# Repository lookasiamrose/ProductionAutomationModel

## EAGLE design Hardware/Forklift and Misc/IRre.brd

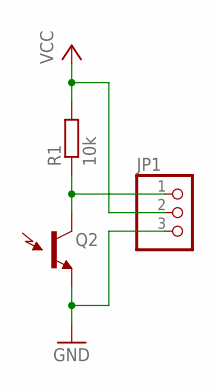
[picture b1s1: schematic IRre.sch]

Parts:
JP1: PINHD-1X3; 1X03
Q2: LTR-301
R1: 10k; R0805

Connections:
GND: JP1.3, Q2.E (E1)
unnamed: JP1.1, Q2.C (C1), R1.1
VCC: JP1.2, R1.2

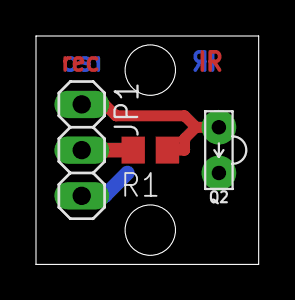
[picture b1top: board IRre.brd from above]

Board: 2 copper layers, 12.4 x 12.7 mm, 3 parts (0 on the bottom side), 3 nets.

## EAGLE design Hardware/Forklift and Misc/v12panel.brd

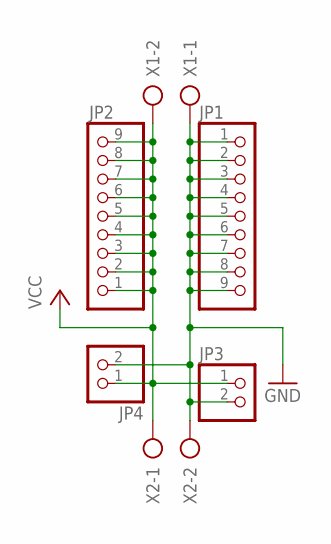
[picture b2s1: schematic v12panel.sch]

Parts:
JP1, JP2: PINHD-1X9; 1X09
JP3, JP4: PINHD-1X2; 1X02
X1, X2: AK500/2

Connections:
GND: JP1.1, JP1.2, JP1.3, JP1.4, JP1.5, JP1.6, JP1.7, JP1.8, JP1.9, JP3.2, JP4.2, X1.1, X2.2
VCC: JP2.1, JP2.2, JP2.3, JP2.4, JP2.5, JP2.6, JP2.7, JP2.8, JP2.9, JP3.1, JP4.1, X1.2, X2.1

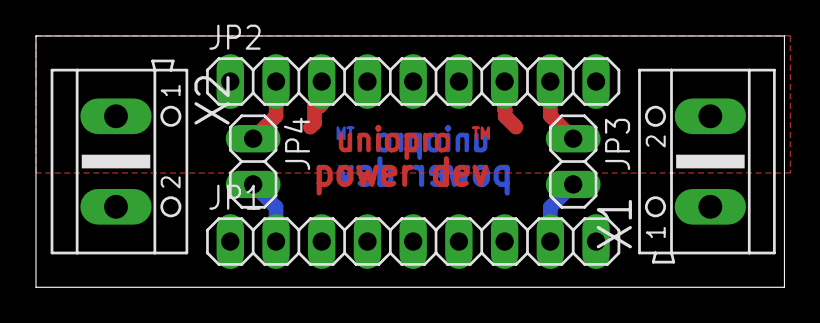
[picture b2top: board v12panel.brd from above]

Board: 2 copper layers, 41.6 x 14.0 mm, 6 parts (0 on the bottom side), 2 nets.

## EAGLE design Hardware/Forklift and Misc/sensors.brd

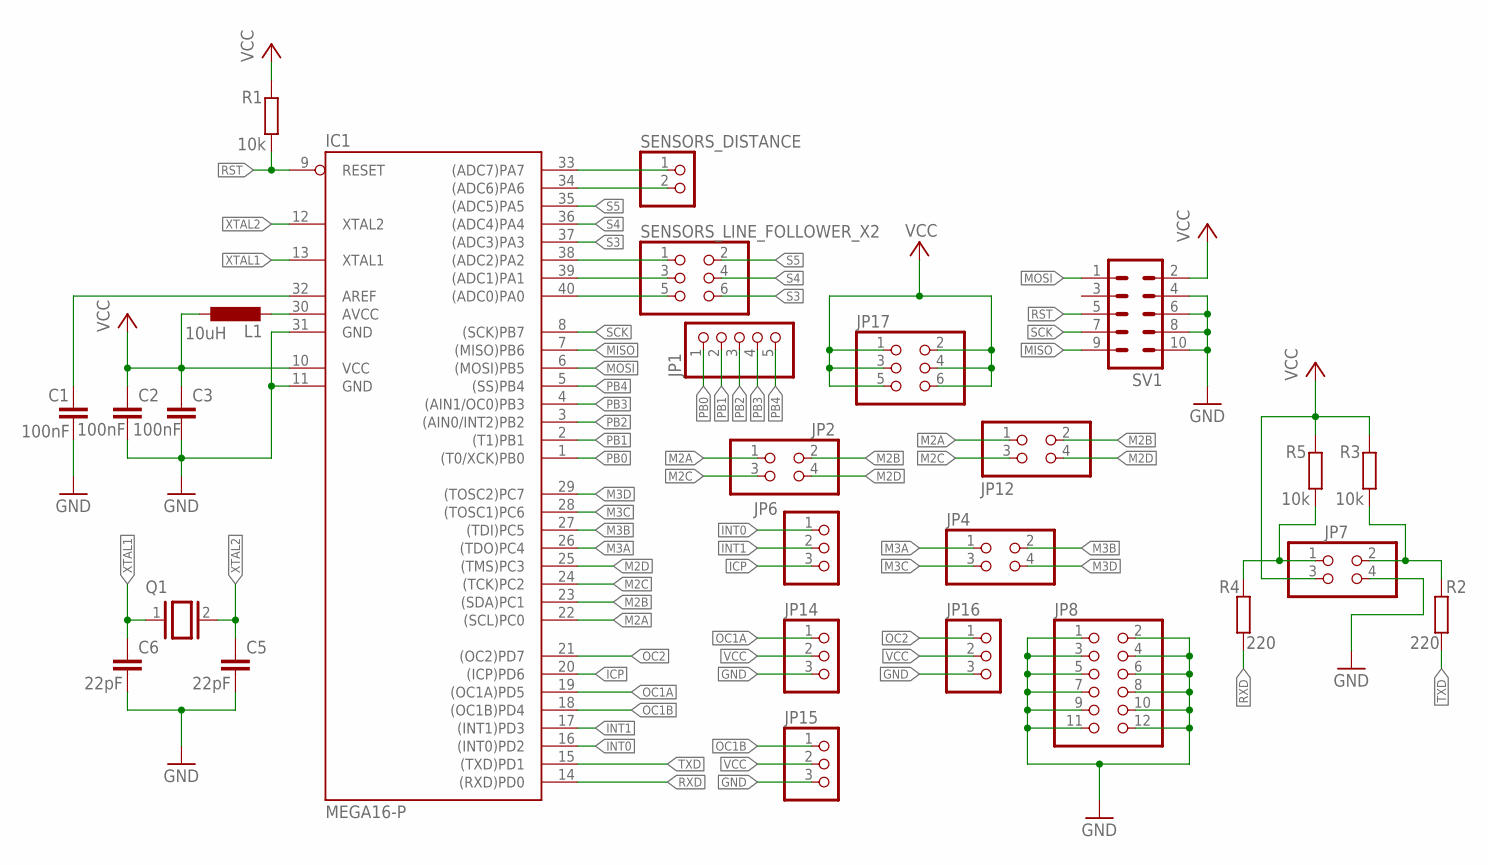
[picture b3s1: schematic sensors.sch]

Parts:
C1, C2, C3: 100nF; C0805
C5, C6: 22pF; C0805
IC1: MEGA16-P; DIL40
JP1: PINHD-1X5; 1X05
JP2, JP4, JP7, JP12: PINHD-2X2; 2X02
JP6, JP14, JP15, JP16: PINHD-1X3; 1X03
JP8: PINHD-2X6; 2X06
JP17: PINHD-2X3; 2X03
L1: 10uH; 0207/7
Q1: XTAL/S; QS
R1, R3, R5: 10k; R0805
R2, R4: 220; R0805
SENSORS_DISTANCE: PINHD-1X2; 1X02
SENSORS_LINE_FOLLOWER_X2: PINHD-2X3; 2X03
SV1: ML10

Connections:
ADC6: IC1.34 ((ADC6)PA6), SENSORS_DISTANCE.2
GND: C1.2, C2.2, C3.2, C5.2, C6.2, IC1.11 (GND), IC1.31 (GND), JP7.4, JP8.1, JP8.2, JP8.3, JP8.4, JP8.5, JP8.6, JP8.7, JP8.8, JP8.9, JP8.10, JP8.11, JP8.12, JP14.3, JP15.3, JP16.3, SV1.4, SV1.6, SV1.8, SV1.10
ICP: IC1.20 ((ICP)PD6), JP6.3
INT0: IC1.16 ((INT0)PD2), JP6.1
INT1: IC1.17 ((INT1)PD3), JP6.2
M2A: IC1.22 ((SCL)PC0), JP2.1, JP12.1
M2B: IC1.23 ((SDA)PC1), JP2.2, JP12.2
M2C: IC1.24 ((TCK)PC2), JP2.3, JP12.3
M2D: IC1.25 ((TMS)PC3), JP2.4, JP12.4
M3A: IC1.26 ((TDO)PC4), JP4.1
M3B: IC1.27 ((TDI)PC5), JP4.2
M3C: IC1.28 ((TOSC1)PC6), JP4.3
M3D: IC1.29 ((TOSC2)PC7), JP4.4
MISO: IC1.7 ((MISO)PB6), SV1.9
MOSI: IC1.6 ((MOSI)PB5), SV1.1
unnamed: JP7.1, R4.2, R5.1
unnamed: JP7.2, R2.2, R3.1
unnamed: C1.1, IC1.32 (AREF)
unnamed: IC1.30 (AVCC), L1.2
unnamed: IC1.33 ((ADC7)PA7), SENSORS_DISTANCE.1
OC1A: IC1.19 ((OC1A)PD5), JP14.1
OC1B: IC1.18 ((OC1B)PD4), JP15.1
OC2: IC1.21 ((OC2)PD7), JP16.1
PB0: IC1.1 ((T0/XCK)PB0), JP1.1
PB1: IC1.2 ((T1)PB1), JP1.2
PB2: IC1.3 ((AIN0/INT2)PB2), JP1.3
PB3: IC1.4 ((AIN1/OC0)PB3), JP1.4
PB4: IC1.5 ((SS)PB4), JP1.5
RST: IC1.9 (RESET), R1.1, SV1.5
RXD: IC1.14 ((RXD)PD0), R4.1
S0: IC1.40 ((ADC0)PA0), SENSORS_LINE_FOLLOWER_X2.5
S1: IC1.39 ((ADC1)PA1), SENSORS_LINE_FOLLOWER_X2.3
S2: IC1.38 ((ADC2)PA2), SENSORS_LINE_FOLLOWER_X2.1
S3: IC1.37 ((ADC3)PA3), SENSORS_LINE_FOLLOWER_X2.6
S4: IC1.36 ((ADC4)PA4), SENSORS_LINE_FOLLOWER_X2.4
S5: IC1.35 ((ADC5)PA5), SENSORS_LINE_FOLLOWER_X2.2
SCK: IC1.8 ((SCK)PB7), SV1.7
TXD: IC1.15 ((TXD)PD1), R2.1
VCC: C2.1, C3.1, IC1.10 (VCC), JP7.3, JP14.2, JP15.2, JP16.2, JP17.1, JP17.2, JP17.3, JP17.4, JP17.5, JP17.6, L1.1, R1.2, R3.2, R5.2, SV1.2
XTAL1: C6.1, IC1.13 (XTAL1), Q1.1
XTAL2: C5.1, IC1.12 (XTAL2), Q1.2

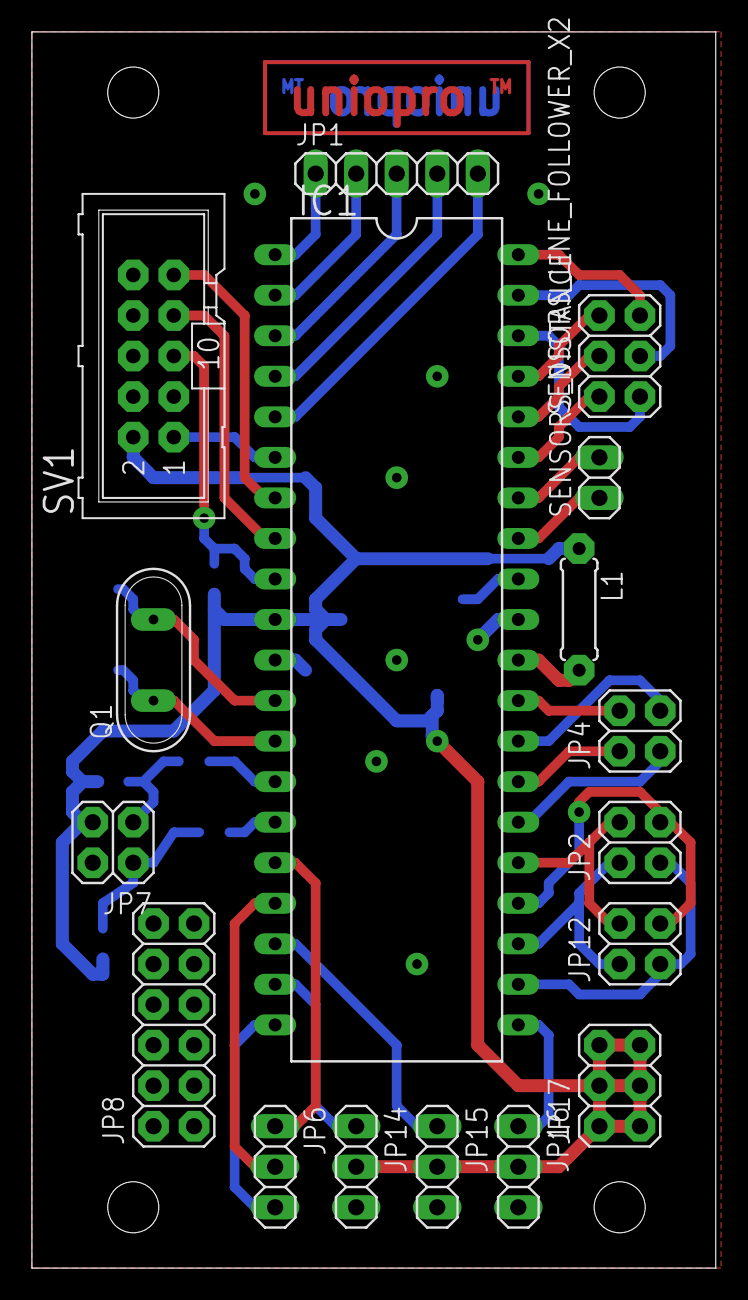
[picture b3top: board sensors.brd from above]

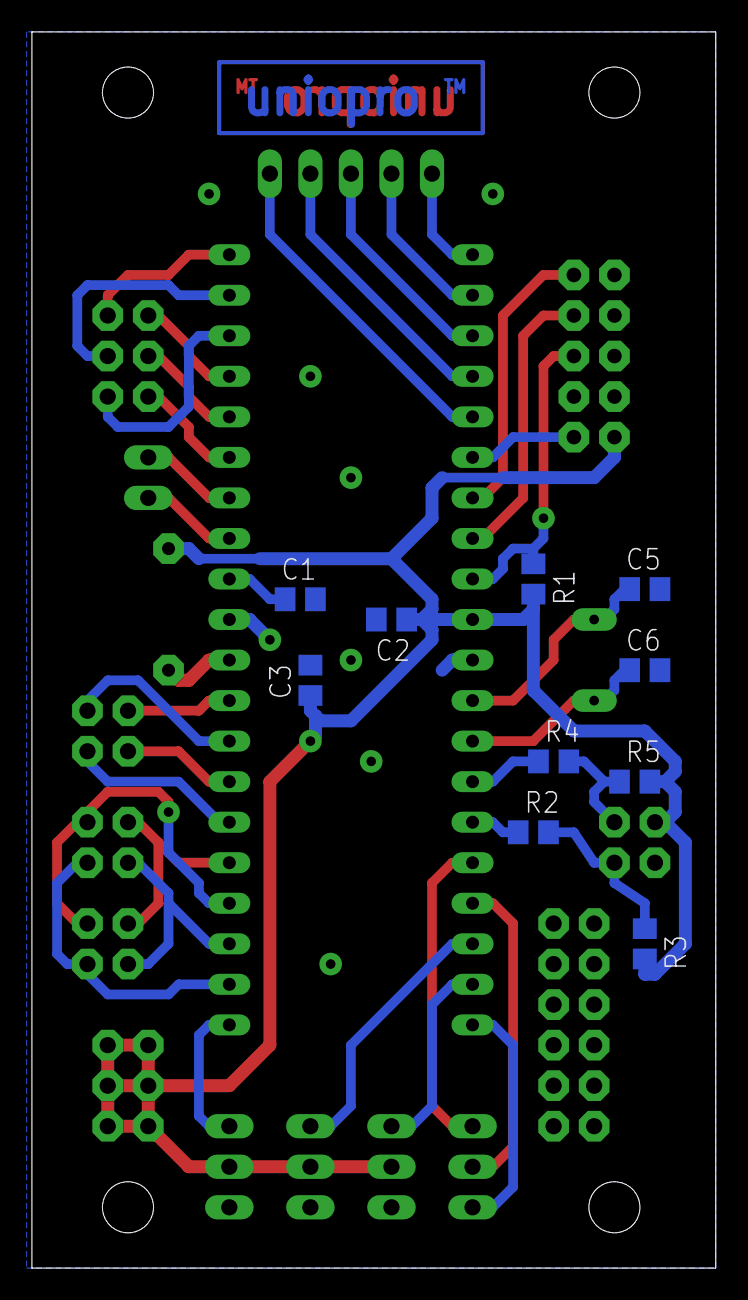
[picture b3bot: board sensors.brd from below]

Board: 2 copper layers, 42.9 x 77.5 mm, 27 parts (10 on the bottom side), 41 nets.

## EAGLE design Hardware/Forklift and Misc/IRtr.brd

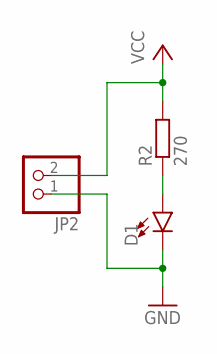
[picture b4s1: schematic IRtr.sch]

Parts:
D1: LED-IRSIDE_EMITTER; LTE-302
JP2: PINHD-1X2; 1X02
R2: 270; R0805

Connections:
GND: D1.C, JP2.1
unnamed: D1.A, R2.1
VCC: JP2.2, R2.2

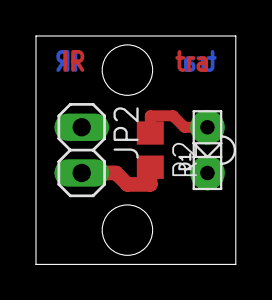
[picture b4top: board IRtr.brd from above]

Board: 2 copper layers, 11.1 x 12.7 mm, 3 parts (0 on the bottom side), 3 nets.

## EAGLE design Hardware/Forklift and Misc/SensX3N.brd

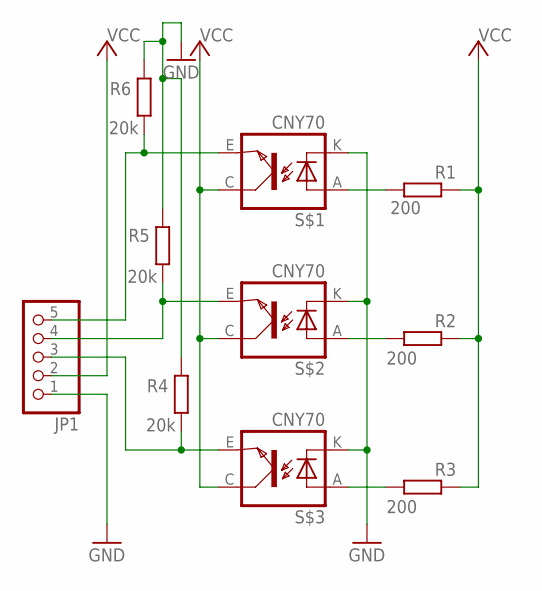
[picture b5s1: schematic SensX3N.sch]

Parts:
JP1: PINHD-1X5; 1X05
R1, R2, R3: 200; R0805
R4, R5, R6: 20k; R0805
S$1, S$2, S$3: CNY70; 4

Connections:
GND: JP1.1, R4.2, R5.2, R6.2, S$1.K (C), S$2.K (C), S$3.K (C)
unnamed: JP1.5, R6.1, S$1.E (EMI)
unnamed: JP1.4, R5.1, S$2.E (EMI)
unnamed: JP1.3, R4.1, S$3.E (EMI)
unnamed: R2.1, S$2.A
unnamed: R1.1, S$1.A
unnamed: R3.1, S$3.A
VCC: JP1.2, R1.2, R2.2, R3.2, S$1.C (COL), S$2.C (COL), S$3.C (COL)

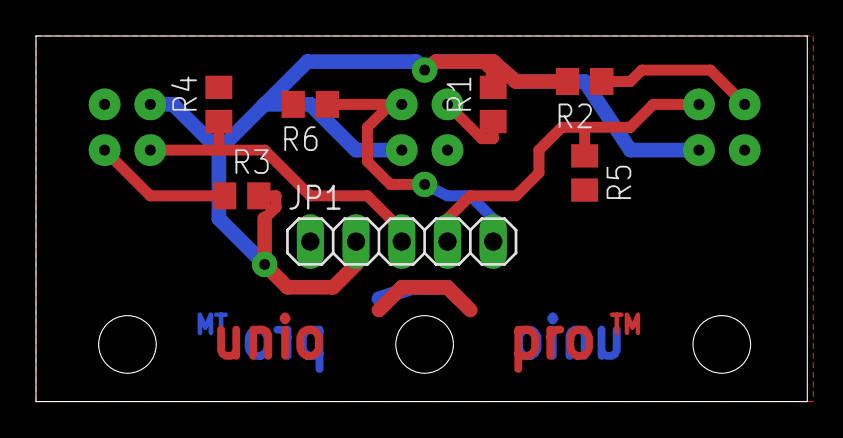
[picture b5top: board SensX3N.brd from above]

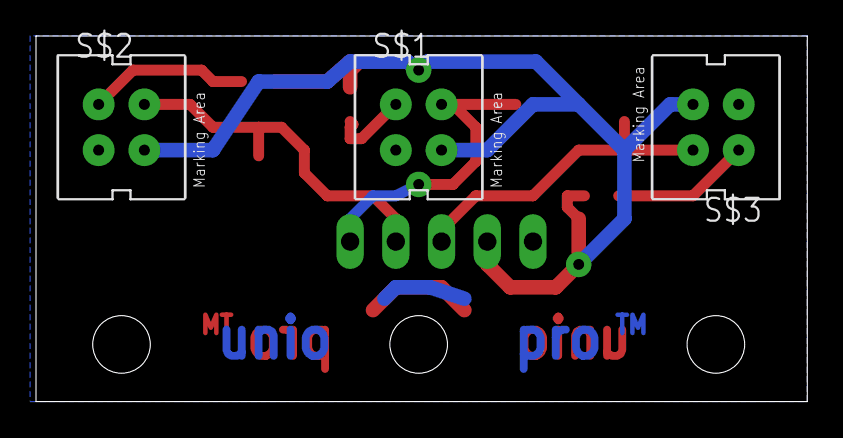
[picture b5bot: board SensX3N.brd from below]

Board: 2 copper layers, 42.9 x 20.3 mm, 10 parts (3 on the bottom side), 8 nets.

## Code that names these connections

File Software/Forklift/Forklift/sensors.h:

/*
 * sensors.h
 *
 * Created: 13.07.2017 18:31:46
 *  Author: lukasz.jamroz
 */ 


#ifndef SENSORS_H_
#define SENSORS_H_

#include <avr/io.h>
#include <avr/interrupt.h>

// -- EDITABLE

#define SERVO_ORDERS_TOTAL_NUMBER 13 //always +1 because index zero is reserved
#define STEPPER_ORDERS_TOTAL_NUMBER 24 //always +1 because index zero is reserved
#define ORDERS_TOTAL_SENSORS_ORDERS_NUMBER 24 //always +1 because index zero is reserved

/* ORDER TYPE */
enum Orders_Barrier_Device{ STEPPER_DEVICE, SERVO_DEVICE, SENSOR_DEVICE, NUM_OF_DIFF_DEVICES };
	 
typedef struct Orders_Barrier
{
	enum Orders_Barrier_Device device;
	uint8_t value;
} Orders_Barrier;

uint8_t orders_get_barrier(enum Orders_Barrier_Device barrier_device_arg, uint8_t barrier_index_arg);
uint8_t orders_get_barrier_index(enum Orders_Barrier_Device barrier_device_arg, uint8_t customer_barrier_arg);

// SENSORS ANALOG INPUT
#define SENSORS_IN_PORT   PORTA
#define SENSORS_IN_DDR    DDRA
#define SENSORS_IN_A      PA0
#define SENSORS_IN_B      PA1
#define SENSORS_IN_C      PA2

#define KEY_DDR     DDRB
#define KEY_PORT    PORTB
#define KEY_PIN     PINB
#define KEY0        PB0   //Button on PB0
#define KEY1        PB1   //Button on PB1

// -- END OF EDITABLE

volatile uint16_t sensors_sensors[3];
volatile uint8_t  sensors_decision;

// PRIV
void sensors_read_adc();
// 
void sensors_init();
uint8_t get_key_press( uint8_t key_mask );
void buttons_init_io(void);

uint8_t debounce_cnt;
volatile uint8_t key_press;
uint8_t key_state;

#endif /* SENSORS_H_ */

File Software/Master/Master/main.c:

#define F_CPU 2000000UL
#include <avr/io.h>
#include <avr/interrupt.h>
#include <util/delay.h>
#include <string.h>
#include "hd44780.h"
#include "usart_driver.h"

#define ORDER_SINGLE_SIZE 18

typedef struct Orders_Order
{
	uint8_t ordersString[ORDER_SINGLE_SIZE];
} Orders_Order;


#define ORDERS_BUFFOR_SIZE 1024
#define ORDERS_LIST_SIZE 64

volatile uint8_t ordersBuffor[ORDERS_BUFFOR_SIZE];
volatile uint8_t globalI;
volatile Orders_Order forkliftOrders[ORDERS_LIST_SIZE];
volatile uint8_t globalOrders;
volatile Orders_Order gantryOrders[ORDERS_LIST_SIZE];
volatile uint8_t globalOrdersGantry;
volatile uint8_t globalType;
volatile uint8_t globalFlag;
volatile char * message;

//#################################### UART
#define USART_SLAVES_PORT USARTD0 /* Define select Usart */
USART_data_t USART_SLAVES; /* USART data struct */

#define USART_MOTHER_DEVICE_PORT USARTE0 /* Define select Usart */
USART_data_t USART_MOTHER_DEVICE; /* USART data struct */

#define USART_GANTRY_DEVICE_PORT USARTF0 /* Define select Usart */
USART_data_t USART_GANTRY_DEVICE; /* USART data struct */

void uartInit( void )
{
	//PORTD.DIRSET = PIN3_bm; /* PD3 (TXD0) as output. */
	//PORTD.DIRCLR = PIN2_bm; /* PD2 (RXD0) as input. */
	
	PORTD_REMAP |= 0x16; //See page 152 in datasheet, remaps the USART0
	
	PORTD_OUTSET = PIN7_bm; //Let's make PC7 as TX
	PORTD_DIRSET = PIN7_bm; //TX pin as output
	
	PORTD_OUTCLR = PIN6_bm;
	PORTD_DIRCLR = PIN6_bm; //PC6 as RX
	
	PORTF_OUTSET = PIN3_bm; //Let's make PC7 as TX
	PORTF_DIRSET = PIN3_bm; //TX pin as output
	
	//PORTF_OUTCLR = PIN2_bm;
	//PORTF_DIRCLR = PIN2_bm; //PC6 as RX
	
	/* Use USARTC0 and initialize buffers. */
	USART_InterruptDriver_Initialize(&USART_SLAVES,&USART_SLAVES_PORT,USART_DREINTLVL_LO_gc);
	USART_InterruptDriver_Initialize(&USART_GANTRY_DEVICE,&USART_GANTRY_DEVICE_PORT,USART_DREINTLVL_LO_gc);
	USART_InterruptDriver_Initialize(&USART_MOTHER_DEVICE,&USART_MOTHER_DEVICE_PORT,USART_DREINTLVL_LO_gc);
	/* USARTC0, 8 Data bits, No Parity, 1 Stop bit. */
	USART_Format_Set(USART_SLAVES.usart,USART_CHSIZE_8BIT_gc,
	USART_PMODE_DISABLED_gc,false);
	USART_Format_Set(USART_GANTRY_DEVICE.usart,USART_CHSIZE_8BIT_gc,
	USART_PMODE_DISABLED_gc,false);
	USART_Format_Set(USART_MOTHER_DEVICE.usart,USART_CHSIZE_8BIT_gc,
	USART_PMODE_DISABLED_gc,false);
	/* Enable RXC interrupt. */
	USART_RxdInterruptLevel_Set(USART_SLAVES.usart, USART_RXCINTLVL_LO_gc);
	USART_RxdInterruptLevel_Set(USART_GANTRY_DEVICE.usart, USART_RXCINTLVL_LO_gc);
	USART_RxdInterruptLevel_Set(USART_MOTHER_DEVICE.usart, USART_RXCINTLVL_LO_gc);
	
	/* calculate Baudrate = (1/(16*(((I/O clock frequency)/Baudrate)-1) = 12 */
	/* BSEL[11:0]-Wert bei 32MHz Takt und BSCALE[3:0]==0: */
	/* 207 : 9600 */
	/* 103 : 19200 */
	/* 51 : 38400 */
	/* 34 : 57600 */
	/* 16 : 115200 */
	USART_Baudrate_Set(&USART_SLAVES_PORT, 12, 0);
	USART_Baudrate_Set(&USART_MOTHER_DEVICE_PORT, 12, 0);
	USART_Baudrate_Set(&USART_GANTRY_DEVICE_PORT, 12, 0);
	/* Enable both RX and TX. */
	USART_Rx_Enable(USART_SLAVES.usart);
	USART_Tx_Enable(USART_SLAVES.usart);
	
	USART_Rx_Enable(USART_MOTHER_DEVICE.usart);
	USART_Tx_Enable(USART_MOTHER_DEVICE.usart);
	
	//USART_Rx_Enable(USART_GANTRY_DEVICE.usart);
	USART_Tx_Enable(USART_GANTRY_DEVICE.usart);
	
	PORTE_REMAP |= 0x16; //See page 152 in datasheet, remaps the USART0
	
	PORTE_OUTSET = PIN7_bm; //Let's make PC7 as TX
	PORTE_DIRSET = PIN7_bm; //TX pin as output
	
	PORTE_OUTCLR = PIN6_bm;
	PORTE_DIRCLR = PIN6_bm; //PC6 as RX
	
	/* Enable PMIC interrupt level low. */
	PMIC.CTRL |= PMIC_LOLVLEN_bm;
}

void addCharToOrdersBuffor(char temporary)
{
	ordersBuffor[globalI] = temporary;
	if( globalI == (ORDERS_BUFFOR_SIZE - 1) )
	{
		globalI = 0;
	}else
		globalI++;
}

void showOrdersBufferToLCD()
{
	LcdClear();
	uint16_t i;
	for(i = 0; i< ORDERS_BUFFOR_SIZE; i++)
	{
		LcdDec(ordersBuffor[i]);
		if(i == 4){
			 Lcd2;
		}
	}	
}

void AddOrderToForklift()
{
	uint8_t ii;
	for(ii =0;ii<ORDER_SINGLE_SIZE;ii++)
	{
		forkliftOrders[globalOrders].ordersString[ORDER_SINGLE_SIZE-1-ii] = ordersBuffor[globalI-1-ii];		
	}
	
	if( globalOrders == (ORDERS_LIST_SIZE-1) )
	{
		globalOrders = 0;
	}else
		globalOrders++;
}
void AddOrderToGantry()
{
	uint8_t ii;
	for(ii =0;ii<ORDER_SINGLE_SIZE;ii++)
	{
		gantryOrders[globalOrdersGantry].ordersString[ORDER_SINGLE_SIZE-1-ii] = ordersBuffor[globalI-1-ii];
	}
	
	if( globalOrdersGantry == (ORDERS_LIST_SIZE-1) )
	{
		globalOrdersGantry = 0;
	}else
		globalOrdersGantry++;
}

void showOrderFromStruct(volatile Orders_Order* order, uint8_t sizeToShow)
{
	uint8_t i;
	for(i = 0; i< sizeToShow; i++)
	{
		//LcdDec(order->ordersString[i]);
		LcdWrite(order->ordersString);
	}
}
void sendOrderToSlaves(volatile Orders_Order* order)
{
	uint8_t i;
	for(i = 0; i< ORDER_SINGLE_SIZE; i++)
	{
		usart_putc(&USART_GANTRY_DEVICE,order->ordersString[i]);
	}
}

void sendOrderToGantry(volatile Orders_Order* order)
{
	uint8_t i;
	for(i = 0; i< ORDER_SINGLE_SIZE; i++)
	{
		usart_putc(&USART_GANTRY_DEVICE,order->ordersString[i]);
	}
}

ISR(USARTE0_RXC_vect)
{
	USART_RXComplete(&USART_MOTHER_DEVICE);

	char temporary = usart_getc(&USART_MOTHER_DEVICE);
	addCharToOrdersBuffor(temporary);
	
	if((temporary == '.') || (temporary == '/'))
	{
		if(globalType == 0)
		{
			 AddOrderToForklift();
		}else if(globalType == 1)
		{
			 AddOrderToGantry();
		}
	}
	
	if(temporary == 'Y')
	{			
		globalFlag = 1;
	}
	if(temporary == '_')
	{
		globalType = 1;
	}
}

ISR(USARTD0_DRE_vect)
{
	USART_DataRegEmpty(&USART_SLAVES);
}

ISR(USARTE0_DRE_vect)
{
	USART_DataRegEmpty(&USART_MOTHER_DEVICE);
}

ISR(USARTF0_DRE_vect)
{
	USART_DataRegEmpty(&USART_GANTRY_DEVICE);
}

int main(void) 
{
	cli();
	
	message = " Orders loaded!";
	uartInit();
	
	LcdInit();               
	LcdClear();
	
	Lcd(" Ready for orders list!");
	
	globalI = 0;
	globalOrders = 0;
	globalType = 0;
	globalOrdersGantry = 0;
	globalFlag = 0;
	PORTF_DIRSET = PIN4_bm;
	PORTF.OUTCLR = PIN4_bm;
	
	sei();
	while(1) {
		if(globalFlag == 1)
		{
			LcdClear();
			Lcd(" Orders autotriggered!");
			uint16_t i;
			usart_putc(&USART_GANTRY_DEVICE,'X');
			for(i = 0; i< globalOrders; i++)
			{
				sendOrderToSlaves(&forkliftOrders[i]);
			}
			usart_putc(&USART_GANTRY_DEVICE,'Y');
		
			PORTF.OUTSET = PIN4_bm;
			usart_putc(&USART_GANTRY_DEVICE,'X');
			for(i = 0; i< globalOrdersGantry; i++)
			{
				sendOrderToGantry(&gantryOrders[i]);
			}
			usart_putc(&USART_GANTRY_DEVICE,'Y');
			PORTF.OUTCLR = PIN4_bm;
			
			Lcd2;
			Lcd(" Orders loaded!");
			
			//LcdClear();
			//showOrderFromStruct(&gantryOrders[0], 1);
		
			globalType = 0;
			globalOrdersGantry = 0;
			globalOrders = 0;
			globalI = 0;
			globalFlag = 0;
		}
	}
}

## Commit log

2018-02-11 clean dev version

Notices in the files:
parts and their libraries:
SparkFun-Sensors: Licensing: Creative Commons ShareAlike 4.0 International - https://creativecommons.org/licenses/by-sa/4.0
